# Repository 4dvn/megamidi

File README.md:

# megamidi

USB MIDI controller on ATMega328P with V-USB. More details [on the Hackaday.io project page](https://hackaday.io/project/8729-megaminimidi).

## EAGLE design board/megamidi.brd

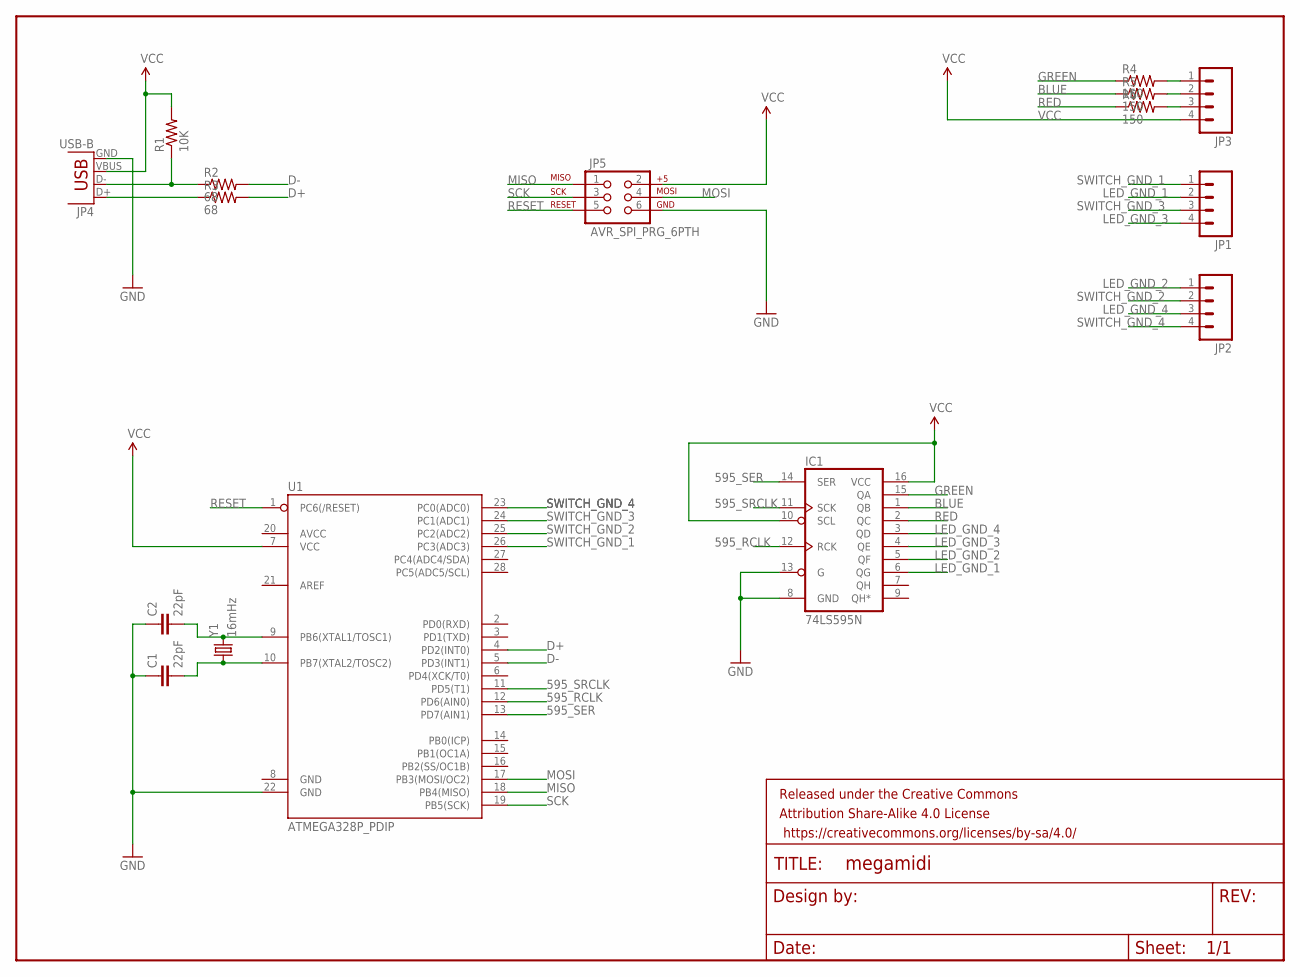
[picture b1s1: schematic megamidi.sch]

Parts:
C1, C2: 22pF; CAP-PTH-SMALL
FRAME1: FRAME-LETTER; CREATIVE_COMMONS
IC1: 74LS595N; DIL16
JP1, JP2, JP3: M04PTH; 1X04
JP4: USB-B; USB-B-PTH
JP5: AVR_SPI_PRG_6PTH; 2X3
R1: 10K; AXIAL-0.1
R2, R3: 68; AXIAL-0.1
R4, R5, R6: 150; AXIAL-0.1
U1: ATMEGA328P_PDIP; DIL28-3
Y1: 16mHz; HC49US

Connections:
595_RCLK: IC1.12 (RCK), U1.12 (PD6(AIN0))
595_SER: IC1.14 (SER), U1.13 (PD7(AIN1))
595_SRCLK: IC1.11 (SCK), U1.11 (PD5(T1))
BLUE: IC1.1 (QB), R5.P$1 (1)
D+: R3.P$2 (2), U1.4 (PD2(INT0))
D-: R2.P$2 (2), U1.5 (PD3(INT1))
GND: C1.1, C2.1, IC1.8 (GND), IC1.13 (G), JP4.GND, JP5.6, U1.22 (GND)
GREEN: IC1.15 (QA), R4.P$1 (1)
LED_GND_1: IC1.6 (QG), JP1.2
LED_GND_2: IC1.5 (QF), JP2.1
LED_GND_3: IC1.4 (QE), JP1.4
LED_GND_4: IC1.3 (QD), JP2.3
MISO: JP5.1, U1.18 (PB4(MISO))
MOSI: JP5.4, U1.17 (PB3(MOSI/OC2))
unnamed: JP4.D-, R1.P$1 (1), R2.P$1 (1)
unnamed: JP4.D+, R3.P$1 (1)
unnamed: JP3.3, R6.P$2 (2)
unnamed: JP3.2, R5.P$2 (2)
unnamed: C2.2, U1.9 (PB6(XTAL1/TOSC1)), Y1.2
unnamed: C1.2, U1.10 (PB7(XTAL2/TOSC2)), Y1.1
unnamed: JP3.1, R4.P$2 (2)
RED: IC1.2 (QC), R6.P$1 (1)
RESET: JP5.5, U1.1 (PC6(/RESET))
SCK: JP5.3, U1.19 (PB5(SCK))
SWITCH_GND_1: JP1.1, U1.26 (PC3(ADC3))
SWITCH_GND_2: JP2.2, U1.25 (PC2(ADC2))
SWITCH_GND_3: JP1.3, U1.24 (PC1(ADC1))
SWITCH_GND_4: JP2.4, U1.23 (PC0(ADC0))
VCC: IC1.10 (SCL), IC1.16 (VCC), JP3.4, JP4.VBUS, JP5.2, R1.P$2 (2), U1.7 (VCC)

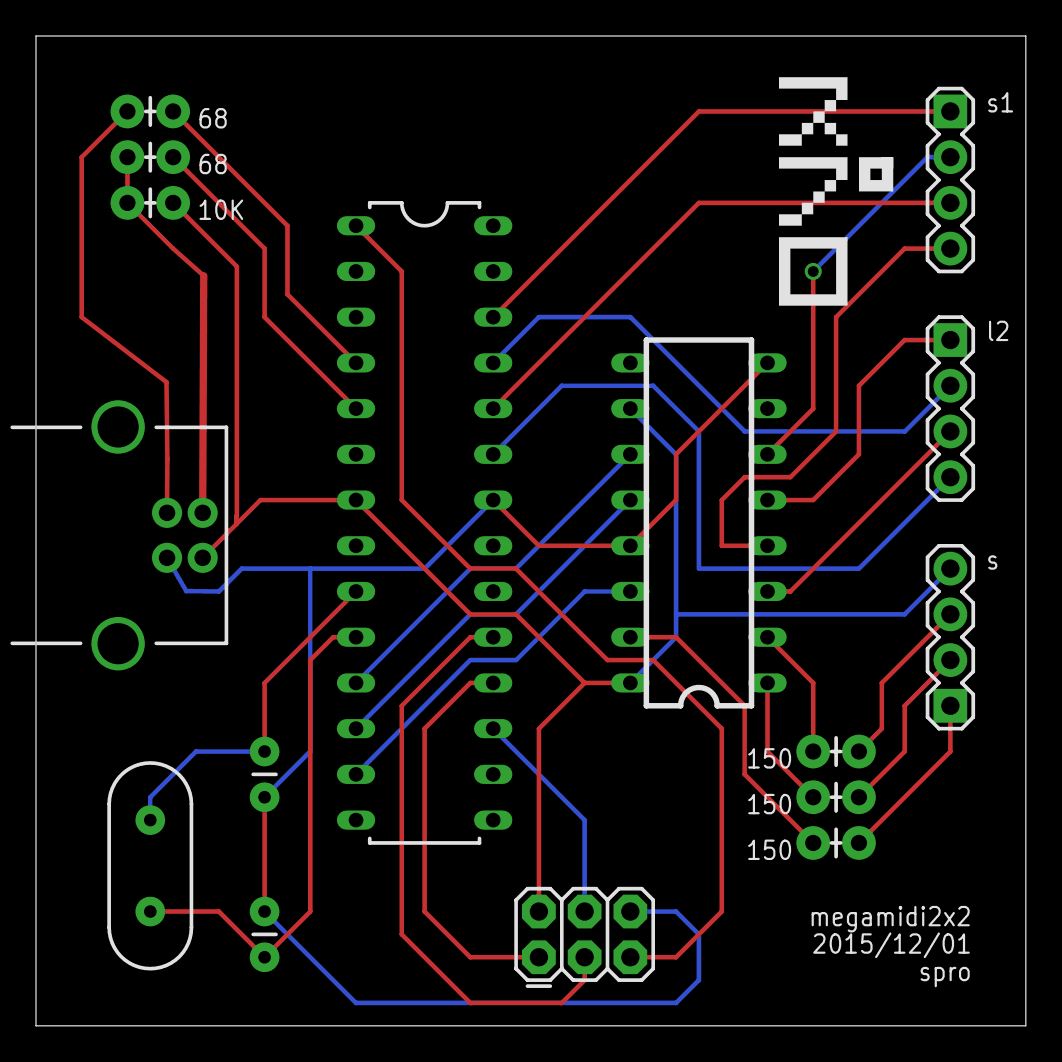
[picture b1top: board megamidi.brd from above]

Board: 2 copper layers, 55.0 x 55.0 mm, 17 parts (0 on the bottom side), 29 nets.

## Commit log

2015-12-18 add box
2015-12-18 svg export of box
2015-12-18 eagle files

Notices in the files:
parts and their libraries:
SparkFun-Capacitors: Licensing: Creative Commons ShareAlike 4.0 International - https://creativecommons.org/licenses/by-sa/4.0
SparkFun-Aesthetics: Released under the Creative Commons Attribution Share-Alike 4.0 License
SparkFun-Aesthetics: https://creativecommons.org/licenses/by-sa/4.0
